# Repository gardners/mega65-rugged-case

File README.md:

# mega65-rugged-case
MEGA65 / MEGAphone Rugged Case Design

Designed to fit a MEGA65 (plus MEGAphone communications hardware)
into a Tactix Large Tough Case

See https://c65gs.blogspot.com/2025/12/megaphone-case-design.html for more information.

Detailed assembly instructions will be developed going forward (it's initially intended only for the MEGAphone development team to implement), as we get community members to replicate it, but it is fairly self-explanatory as you go through, with the following points:
1. The upper file is for the LCD panel and driver boards. 
2. The four lower cuts are for the keyboard, floppy drive, MEGA65 FPGA board and ancilliaries and cellular module plus battery, respectively.
3. All fixings are M3.  All panel spacers are 25mm metal spacers to suit M3 screws.  All fixings and spacers can be purchased in Australia from Jaycar Electronics.  Equivalents will be easily available in other countries.
4. Once the full deck is assembled, it slides fairly easily into the lower-shell of the case, but fits snugly enough that it doesn't need fixing in place.
5. The LCD panel bezel assembly does need fixing in place, and the panel cut-out that holds the driver boards can be laid against the rear of the lid, centred horizontally, and used as a guide for drilling the 3mm holes in the lid.  The vertical positioning pieces allow for vertical adjustment of the position of the panel and it's screws through the case lid, so that the exact vertical positioning of the holes in the lid do not need to be precise, which can otherwise be difficult to achieve.

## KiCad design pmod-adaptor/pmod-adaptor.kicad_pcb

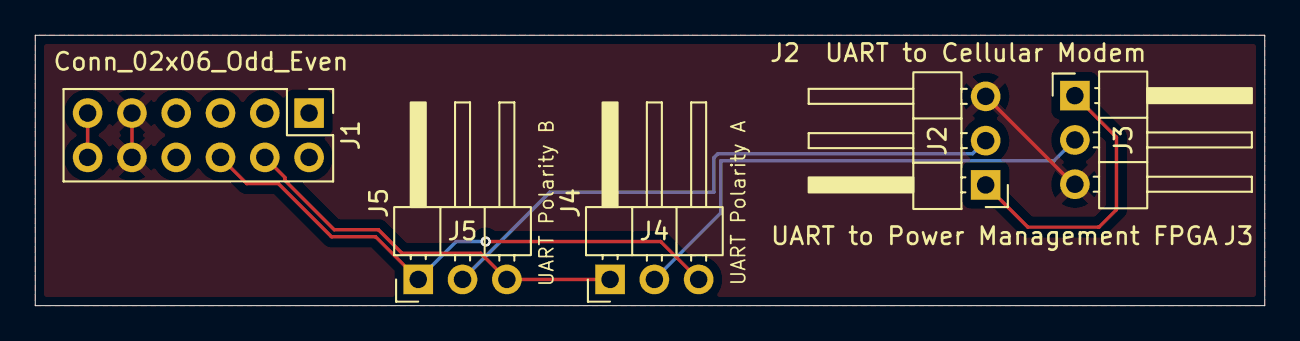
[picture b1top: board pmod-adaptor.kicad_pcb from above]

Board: 2 copper layers, 70.5 x 15.5 mm, 5 parts (0 on the bottom side), 7 nets.

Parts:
J1: Conn_02x06_Odd_Even; PinHeader_2x06_P2.54mm_Vertical
J2: UART to Cellular Modem; PinHeader_1x03_P2.54mm_Horizontal
J3: UART to Power Management FPGA; PinHeader_1x03_P2.54mm_Horizontal
J4: UART Polarity A; PinHeader_1x03_P2.54mm_Horizontal
J5: UART Polarity B; PinHeader_1x03_P2.54mm_Horizontal

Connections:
+3V3: J1.11, J1.12
GND: J1.9, J1.10, J2.3, J3.3
PMOD1_4: J1.4, J4.1, J5.3
PMOD1_6: J1.6, J4.3, J5.1
UART_A: J3.2, J4.2
UART_B: J2.2, J5.2
UART_RELAY: J2.1, J3.1

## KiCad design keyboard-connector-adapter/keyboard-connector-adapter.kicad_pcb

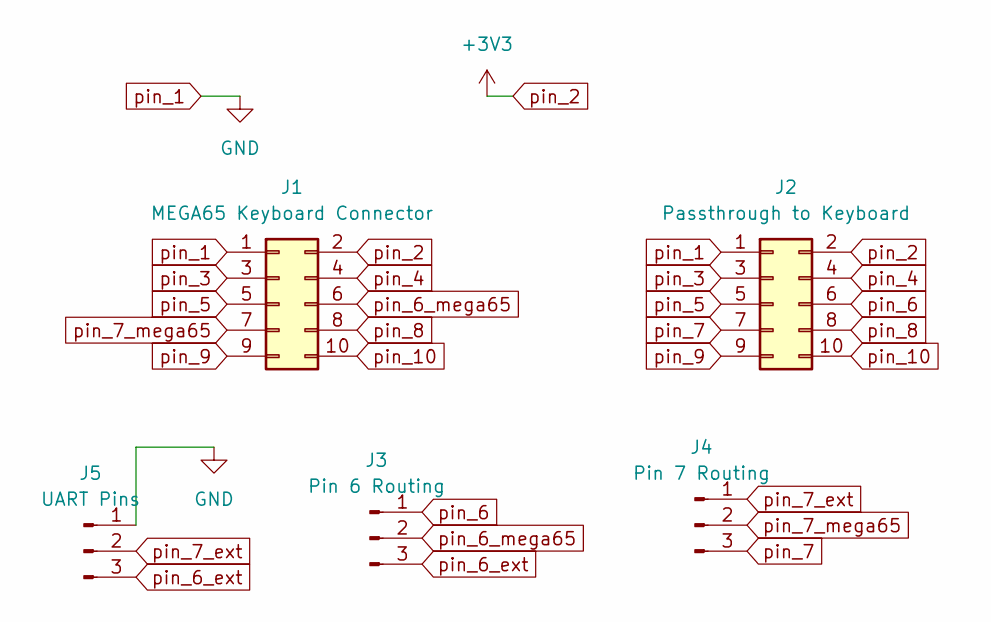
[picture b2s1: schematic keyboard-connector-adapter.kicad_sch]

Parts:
J1: MEGA65 Keyboard Connector; PinSocket_2x05_P2.54mm_Vertical
J2: Passthrough to Keyboard; PinHeader_2x05_P2.54mm_Horizontal
J3: Pin 6 Routing; PinHeader_1x03_P2.54mm_Horizontal
J4: Pin 7 Routing; PinHeader_1x03_P2.54mm_Horizontal
J5: UART Pins; PinHeader_1x03_P2.54mm_Horizontal

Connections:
pin_1: J1.1, J2.1, J5.1
pin_2: J1.2, J2.2
pin_3: J1.3, J2.3
pin_4: J1.4, J2.4
pin_5: J1.5, J2.5
pin_6: J2.6, J3.1
pin_6_ext: J3.3, J5.3
pin_6_mega65: J1.6, J3.2
pin_7: J2.7, J4.3
pin_7_ext: J4.1, J5.2
pin_7_mega65: J1.7, J4.2
pin_8: J1.8, J2.8
pin_9: J1.9, J2.9
pin_10: J1.10, J2.10

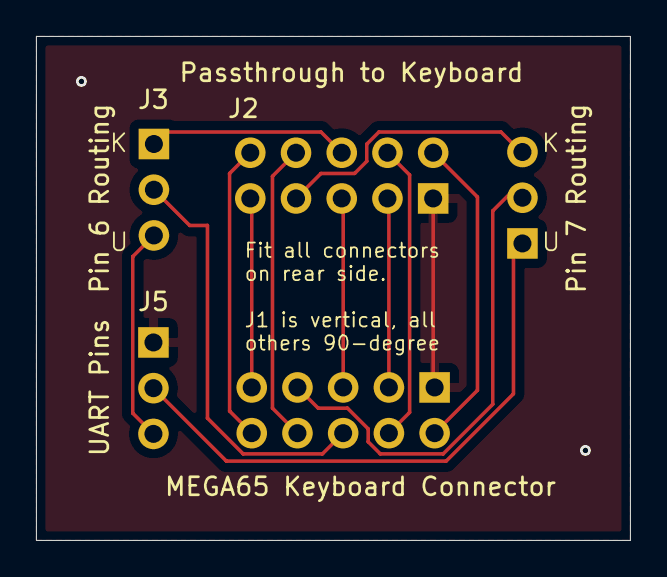
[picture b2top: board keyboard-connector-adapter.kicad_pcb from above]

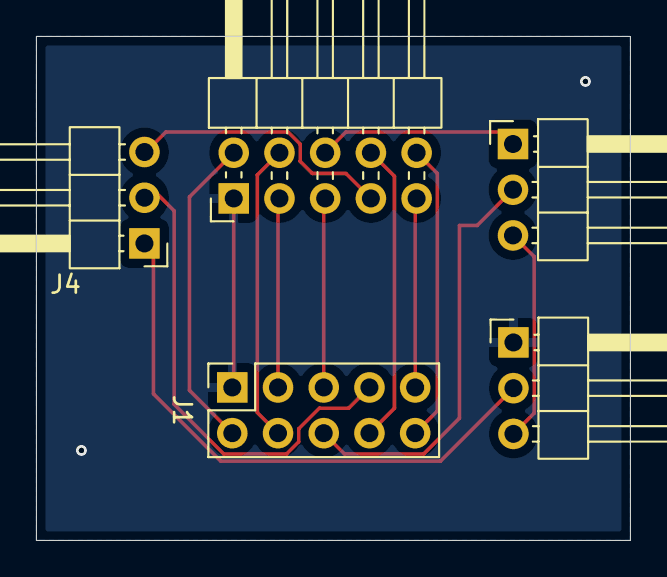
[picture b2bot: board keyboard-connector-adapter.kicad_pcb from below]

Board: 2 copper layers, 33.0 x 28.0 mm, 5 parts (5 on the bottom side), 14 nets.

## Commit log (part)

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2025-11-15 begin designing laser-cut upper piece for LCD panel
2025-11-15 add more holes etc
2025-11-15 update upper design SVG based on first laser-cut attempt
2025-11-15 begin drawing top-plate for lower half
2025-11-22 refinements from next test cut. add phone and disk access cut-outs
2025-11-22 add extra holes for lid mounting
2025-11-22 add LCD panel cables cut-out
2025-11-22 begin work on next layer down
2025-11-22 add securing holes to next deck below keyboard
2025-11-22 more work on lower decks
2025-11-22 adjustments based on next laser cut run
2025-11-22 more refinements following laser cut. path subtractions
2025-11-22 more refinement following more prints
2025-11-24 make upper bracket vertically adjustable
2025-11-29 update upper and lower decks. add lower deck4
2025-11-29 further refining lower case
2025-11-30 more adjustments to lower case
2025-11-30 further refinement
2025-11-30 there is no 5th deck anymore
2025-12-01 update README with basic build instructions
2026-01-03 adjust lower laser cut for MK-II keyboard
2026-01-03 add assembly labels to keyboard deck
2026-01-03 add pseudo-cold-war text to keyboard layer
2026-01-03 more assembly instructions
2026-01-03 use SVG logo. Various minor tweaks
2026-01-03 begin assembly instructions
2026-01-03 work on assembly instructions
2026-01-03 improve POWER and BOOT label positions for switch clearance
2026-01-03 correct hole positions for 5V regulator for cellular modem
2026-01-03 begin documenting fixings on 3rd deck.
2026-01-03 enlarge hole to allow 12V DC:DC to pass through the hole.
2026-01-04 add provision for isolator switch and phone cord path.
2026-01-04 move phone cord path to right hand side so that curly cord can rest at front of keyboard
2026-03-07 import dione refinements to panels
2026-03-07 remove outlines from text
2026-03-07 convert build lines back to lines instead of raster
2026-03-09 3rd rev from Dione
2026-03-09 add keyboard connector adaptor PCB
2026-03-09 plot drill and gerbers
2026-03-14 incorporate feedback from Dione following latest test cut
2026-03-14 fix non-filled morse table bits
